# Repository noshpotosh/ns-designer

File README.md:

# NS Designer

A 36-key ortholinear wireless split keyboard using Kailh PG1316S switches and two XIAO nRF52840 controllers. The selected design is a 17 mm-pitch open tray with a ≤7 mm height target. **It is not yet a validated, complete build kit.**

[Read the buildbook](https://noshpotosh.github.io/ns-designer/). Start with [build readiness](buildbook/chapters/readiness.md) before ordering parts.

## Read and edit

The authoritative text is in `buildbook/chapters/`. Edit Markdown there; the generated HTML is not tracked. Raw HTML in the overview and model chapters preserves interactive figures. Layout, styles and behavior live in `buildbook/template/`; the 3D viewer lives in `buildbook/viewer/`.

With Node.js 22 or newer:

```sh
npm ci
npm run check
npm run preview
```

Open http://localhost:8000/ns-designer/. `npm run build` generates `dist/index.html` with adjacent assets, viewer and downloads. Deploy the **entire dist directory**, not just the HTML. Preview uses a project prefix to catch GitHub Pages path issues. Google Fonts and the pinned Three.js CDN need network access; text, static renders and downloads remain available without them.

## Repository map

| Directory | What belongs here |
|---|---|
| `buildbook/` | Markdown chapters, presentation, static renders and viewer |
| `hardware/pcb/` | Editable left/right KiCad projects, project library, bootstrap/routing/export scripts |
| `hardware/case/` | Parametric concept CAD and render script |
| `references/` | Collected third-party assets and provenance catalog |
| `exports/` | Existing fabrication snapshots and concept models; see [catalog](exports/README.md) |
| `firmware/` | Missing-implementation notice; no buildable ZMK config yet |
| `scripts/` | Website build, preview and validation |

Open each `.kicad_pro` with KiCad 10 and its stock libraries installed. Custom libraries and available models resolve relative to the projects. The XIAO footprint has no 3D model. Firmware and printable per-half cases still need implementation; the right-side reset location and physical fit need validation.

## Hardware workflow

Hardware generation is **manual and separate** from publishing. See [artifact catalog](exports/README.md) for commands. Do not run `generate.py --force` or `route.py` to build the site: they overwrite design work. The committed KiCad projects are the editable source of truth; the bootstrap is not a lossless round-trip.

## GitHub Pages and checks

In repository Settings → Pages, select **GitHub Actions**. The workflow validates pull requests and deploys default-branch pushes (or a manual run on that branch). It uploads only `dist/`; it does not run KiCad or CAD tools. The expected site URL is linked above. Publishing becomes active after these changes are pushed and Pages is configured.

`npm run check` validates the bundle, local links/anchors, download inventory and KiCad relative references. For browser checks:

```sh
npx playwright install chromium
npm run check:browser
```

Browser checks cover desktop/mobile layouts, colorway controls, both 3D variants, and a blocked-CDN fallback. Browser and dependency downloads require network access. These checks do not certify electronics, fabrication output freshness, or mechanical fit.

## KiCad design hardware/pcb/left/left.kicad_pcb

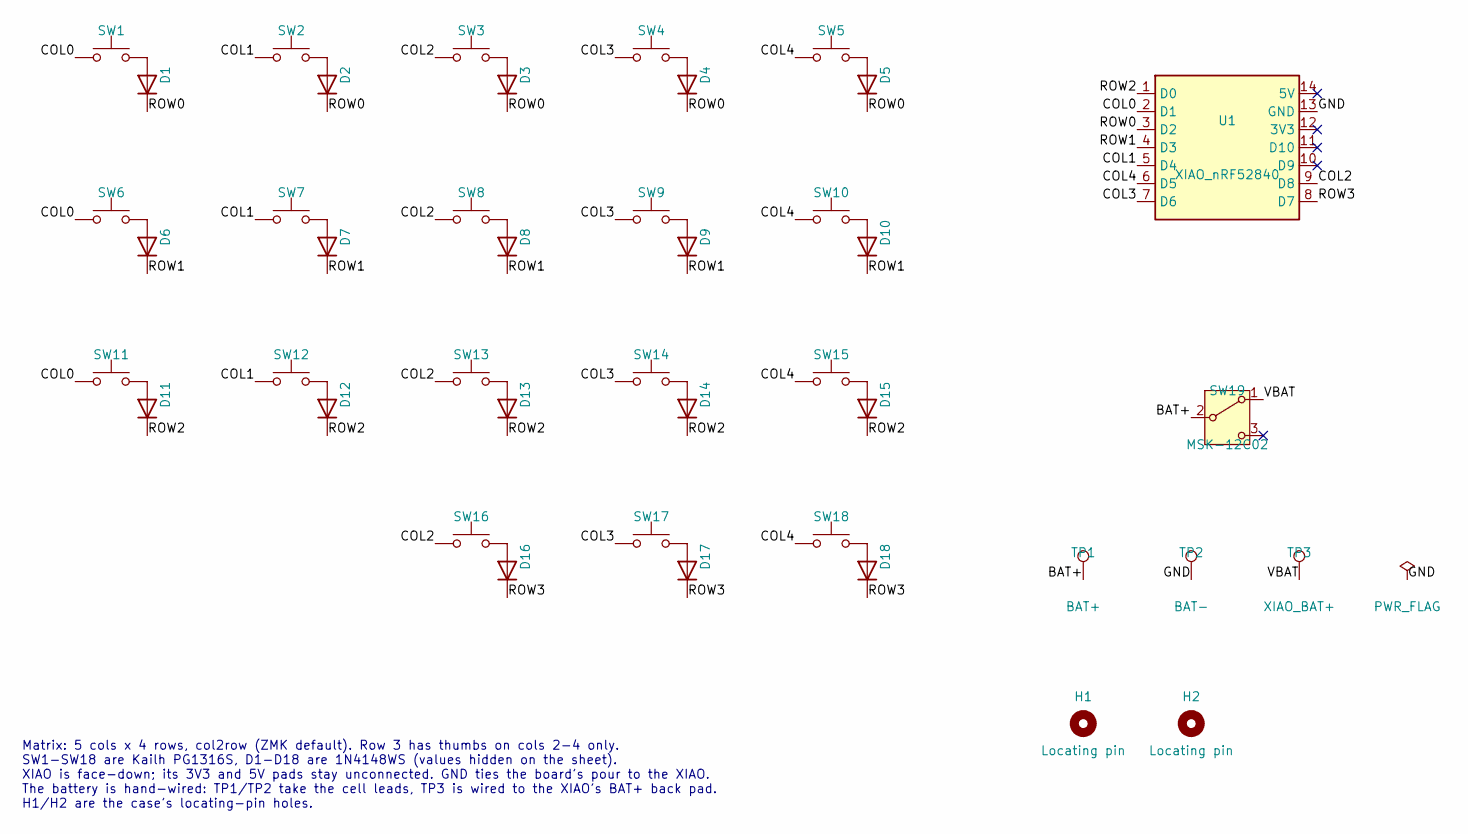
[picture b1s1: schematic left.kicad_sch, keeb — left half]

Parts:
D1, D2, D3, D4, D5, D6, D7, D8, D9, D10, D11, D12, D13, D14, D15, D16, D17, D18: 1N4148WS; D_SOD-323_HandSoldering; LCSC C2128
H1, H2: Locating pin; Post_Locating_D1.0
SW1, SW2, SW3, SW4, SW5, SW6, SW7, SW8, SW9, SW10, SW11, SW12, SW13, SW14, SW15, SW16, SW17, SW18: PG1316S; SW_Kailh_PG1316S_ViaInPad
SW19: MSK-12C02; SW_Slide_MSK-12C02; LCSC C431540
TP1: BAT+; TestPoint_Pad_1.5x1.5mm
TP2: BAT-; TestPoint_Pad_1.5x1.5mm
TP3: XIAO_BAT+; TestPoint_Pad_1.5x1.5mm
U1: XIAO_nRF52840; XIAO_nRF52840_FaceDown

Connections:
/BAT+: SW19.2 (B), TP1.1
/COL0: SW1.1, SW6.1, SW11.1, U1.2 (D1)
/COL1: SW2.1, SW7.1, SW12.1, U1.5 (D4)
/COL2: SW3.1, SW8.1, SW13.1, SW16.1, U1.9 (D8)
/COL3: SW4.1, SW9.1, SW14.1, SW17.1, U1.7 (D6)
/COL4: SW5.1, SW10.1, SW15.1, SW18.1, U1.6 (D5)
/GND: TP2.1, U1.13 (GND)
/ROW0: D1.1 (K), D2.1 (K), D3.1 (K), D4.1 (K), D5.1 (K), U1.3 (D2)
/ROW1: D6.1 (K), D7.1 (K), D8.1 (K), D9.1 (K), D10.1 (K), U1.4 (D3)
/ROW2: D11.1 (K), D12.1 (K), D13.1 (K), D14.1 (K), D15.1 (K), U1.1 (D0)
/ROW3: D16.1 (K), D17.1 (K), D18.1 (K), U1.8 (D7)
/VBAT: SW19.1 (A), TP3.1
unnamed: D1.2 (A), SW1.2
unnamed: D2.2 (A), SW2.2
unnamed: D3.2 (A), SW3.2
unnamed: D4.2 (A), SW4.2
unnamed: D5.2 (A), SW5.2
unnamed: D6.2 (A), SW6.2
unnamed: D7.2 (A), SW7.2
unnamed: D8.2 (A), SW8.2
unnamed: D9.2 (A), SW9.2
unnamed: D10.2 (A), SW10.2
unnamed: D11.2 (A), SW11.2
unnamed: D12.2 (A), SW12.2
unnamed: D13.2 (A), SW13.2
unnamed: D14.2 (A), SW14.2
unnamed: D15.2 (A), SW15.2
unnamed: D16.2 (A), SW16.2
unnamed: D17.2 (A), SW17.2
unnamed: D18.2 (A), SW18.2

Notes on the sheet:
Matrix: 5 cols x 4 rows, col2row (ZMK default). Row 3 has thumbs on cols 2-4 only. SW1-SW18 are Kailh PG1316S, D1-D18 are 1N4148WS (values hidden on the sheet). XIAO is face-down; its 3V3 and 5V pads stay unconnected. GND ties the board's pour to the XIAO. The battery is hand-wired: TP1/TP2 take th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

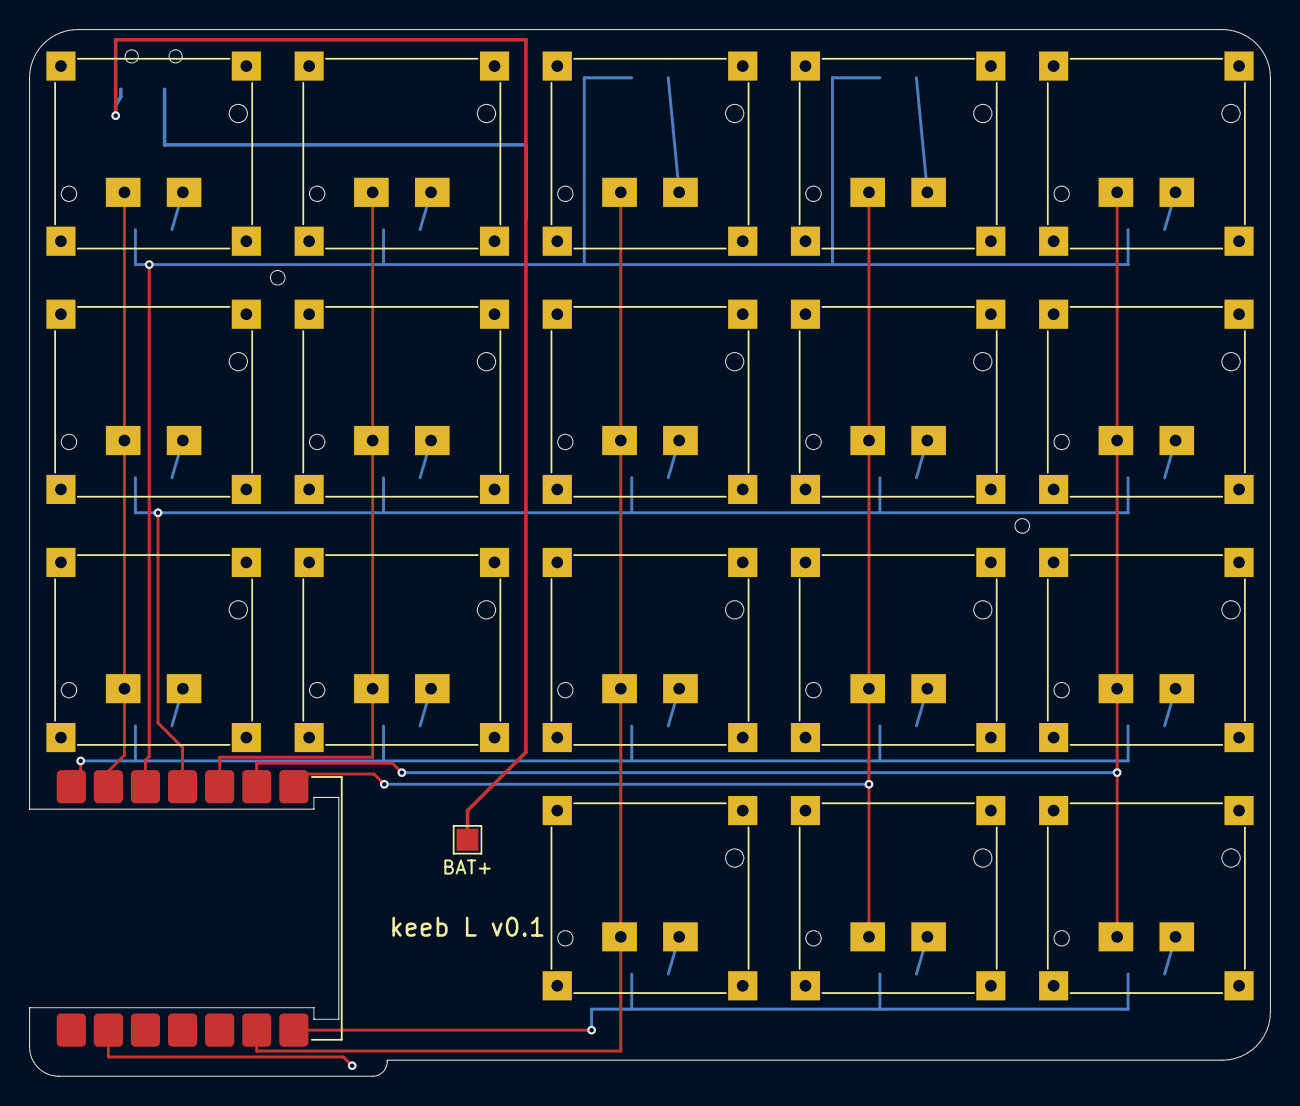
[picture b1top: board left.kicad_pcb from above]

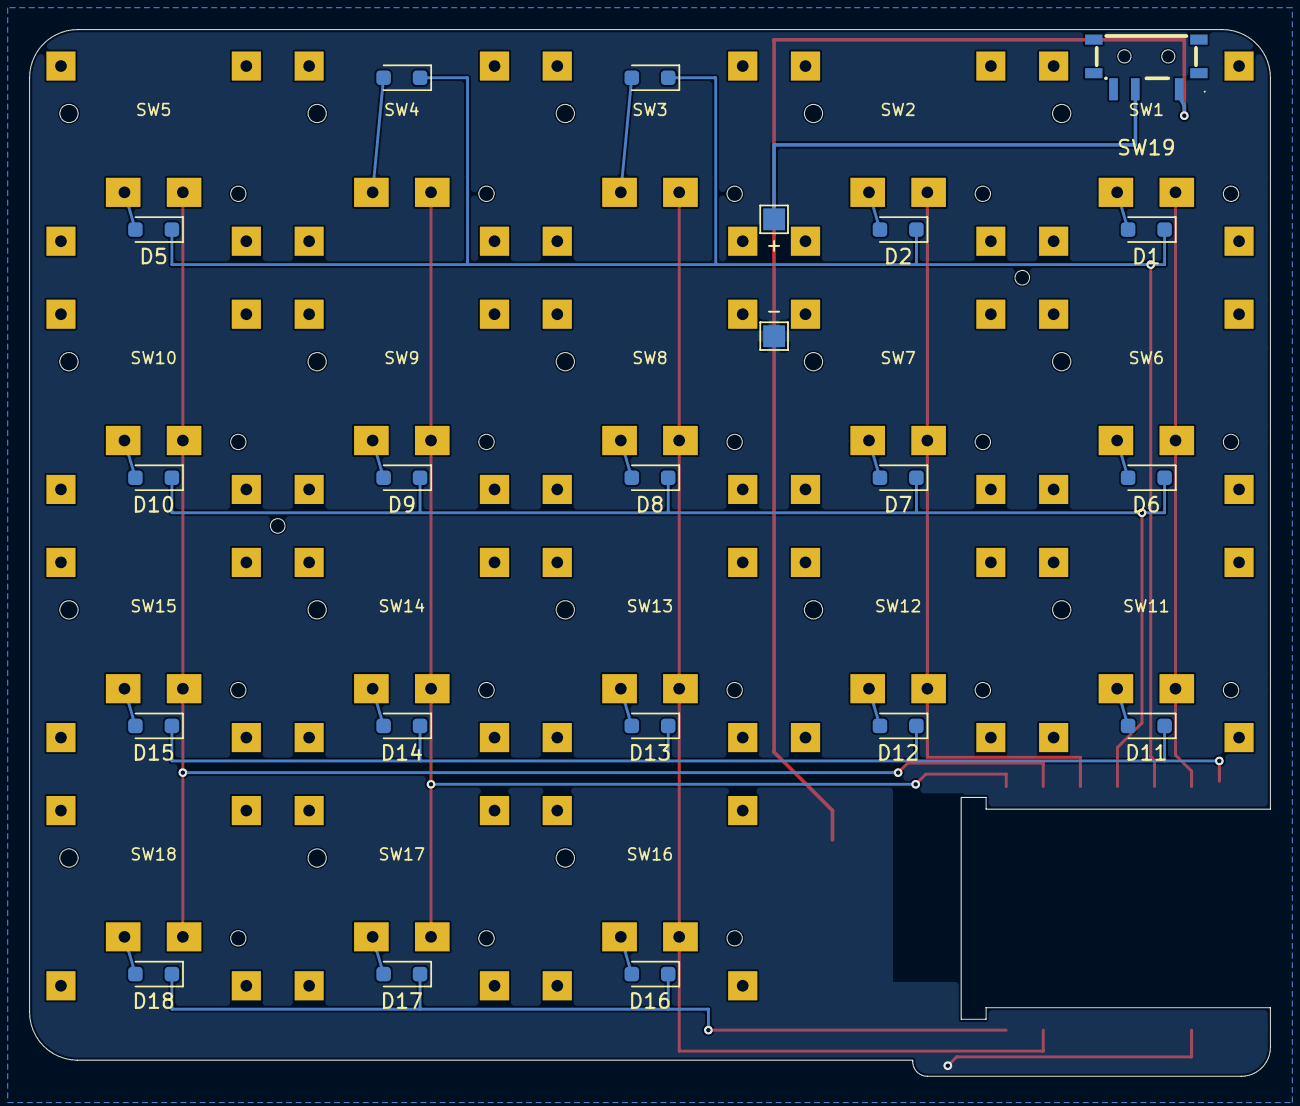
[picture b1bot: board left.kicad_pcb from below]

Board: 2 copper layers, 85.0 x 71.7 mm, 43 parts (21 on the bottom side), 30 nets.
